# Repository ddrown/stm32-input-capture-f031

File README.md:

This was originally designed to accept a very low frequency pwm output (1-50Hz) and measure the SBC's frequency vs the TCXO's. That frequency data can then be fed into chrony's temperature compensation system to result in more stable time for NTP service.

Hardware is a custom designed SBC hat with microcontroller and TCXO

The TCXO's frequency vs temperature curve is measured and stored in flash in order to increase long term frequency accuracy.

The hat also contains an RTC with sub-second precision. Usually i2c RTCs will only tell you time to the nearest second, so you have to poll them to find out when the second changes. The RTC runs off the 32khz crystal, but can be measured in hardware against the TCXO with `clients/rtc compare`

Timers used
* TIM2 - main 32 bit timer, all 4 channels are setup as pwm output (10ms high, 990ms low)
* TIM14 - 16 bit timer, measures RTC vs TCXO on channel 1

Hat pins connected to SBC/stm32 micro:
* pin3 - I2C SDA
* pin5 - I2C SCL
* pin11 - stm32 rst (via jumper)
* pin12 - PPS output CH1
* pin13 - stm32 BOOT0 (via jumper)
* pin18 - SWD dio (via jumper)
* pin22 - SWD clk (via jumper)
* pin33 - PPS output CH2

settings in raspi-config:

i2c enabled
(optional for gps) serial login shell disabled, serial interface enabled

/boot/config.txt:
dtparam=i2c\_arm=on
dtparam=i2c\_arm\_baudrate=400000
\# optional for gps
dtoverlay=pps-gpio,gpiopin=13

stm32 source code:

* Src/system_stm32f0xx.c - bootup, start clocks
* Src/main.c - init peripherals, main loop
* Src/stm32f0xx_hal_msp.c - init irq, init gpio routing, init clocks, etc
* Src/stm32f0xx_it.c - irq handlers (mostly call into HAL)
* Src/adc.c - measure temperature, vcc, and rtc battery
* Src/flash.c - store TCXO parameters in flash
* Src/i2c_slave.c - i2c interface to talk to SBC
* Src/timer.c - manages TIM2, TIM14, and RTC
* Src/uart.c - debug uart interface
* Drivers/STM32F0xx_HAL_Driver - stm32 Hardware Abstraction Layer (HAL)

SBC tool code:

* clients/timestamps-i2c.c - compare SBC system time vs TCXO, request via i2c
* clients/input-capture-i2c.c - compare SBC system frequency vs TCXO, via SBC output pwm
* clients/pi-pwm-setup.c - wiringPi setup SBC output pwm
* clients/pi-pwm-disable.c - wiringPi disable SBC output pwm
* clients/odroid-c2-setup - sysfs setup SBC output pwm
* clients/rtc.c - read/set/sync/manage rtc
* clients/set-calibration-data.c - get/set TCXO calibration data in flash
* clients/ds3231.c - DS3231 RTC i2c client
* clients/pcf2129.c - PCF2129 RTC i2c client
* clients/calibration.c - measure RTC vs TCXO
* clients/dump-adc.c - test comparing floating vs fixed point math

SBC library code:

* clients/adc_calc.c - read ADC data over i2c
* clients/aging.c - estimate TCXO frequency from aging effects
* clients/avg.c - calculate averages
* clients/float.c - convert between native float and i2c compatible
* clients/i2c.c - i2c interface functions
* clients/i2c_registers.c - read stm32's exported data via i2c
* clients/rtc_data.c - convert between RTC data and system time
* clients/tempcomp.c - calculate TCXO's temperature compensation
* clients/timespec.c - struct timespec utilities
* clients/vref_calc.c - adc voltage calculations

Programming the stm32 can be done via openocd on the connected SBC.

Example openocd configuration:
* openocd.cfg - raspberry pi & stlink example
* openocd-odroid.cfg - gpio sysfs on odroid-c2 SBC
* openocd-stm32mp1.cfg - gpio sysfs on stm32mp157a-dk1 SBC

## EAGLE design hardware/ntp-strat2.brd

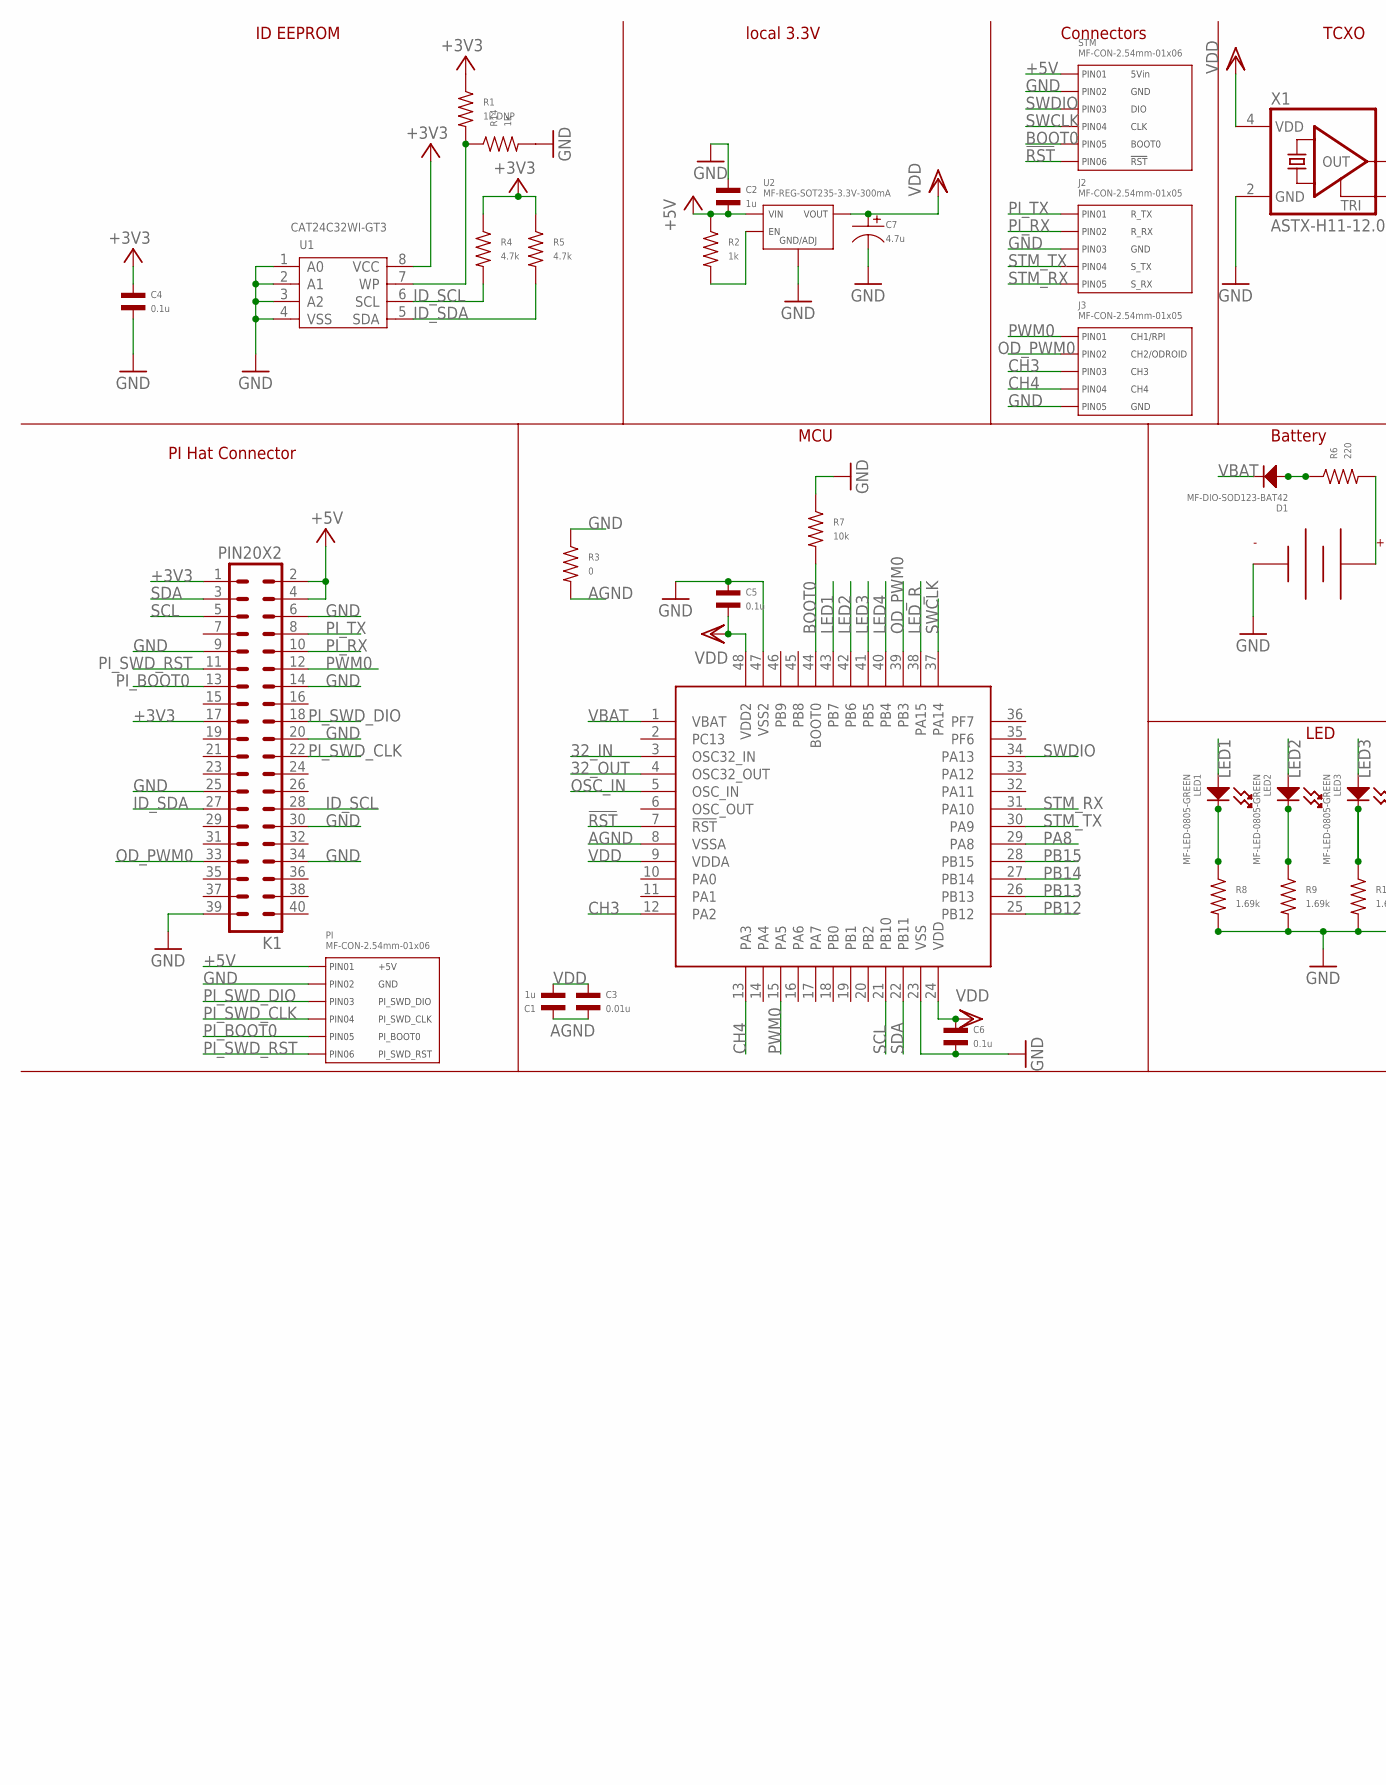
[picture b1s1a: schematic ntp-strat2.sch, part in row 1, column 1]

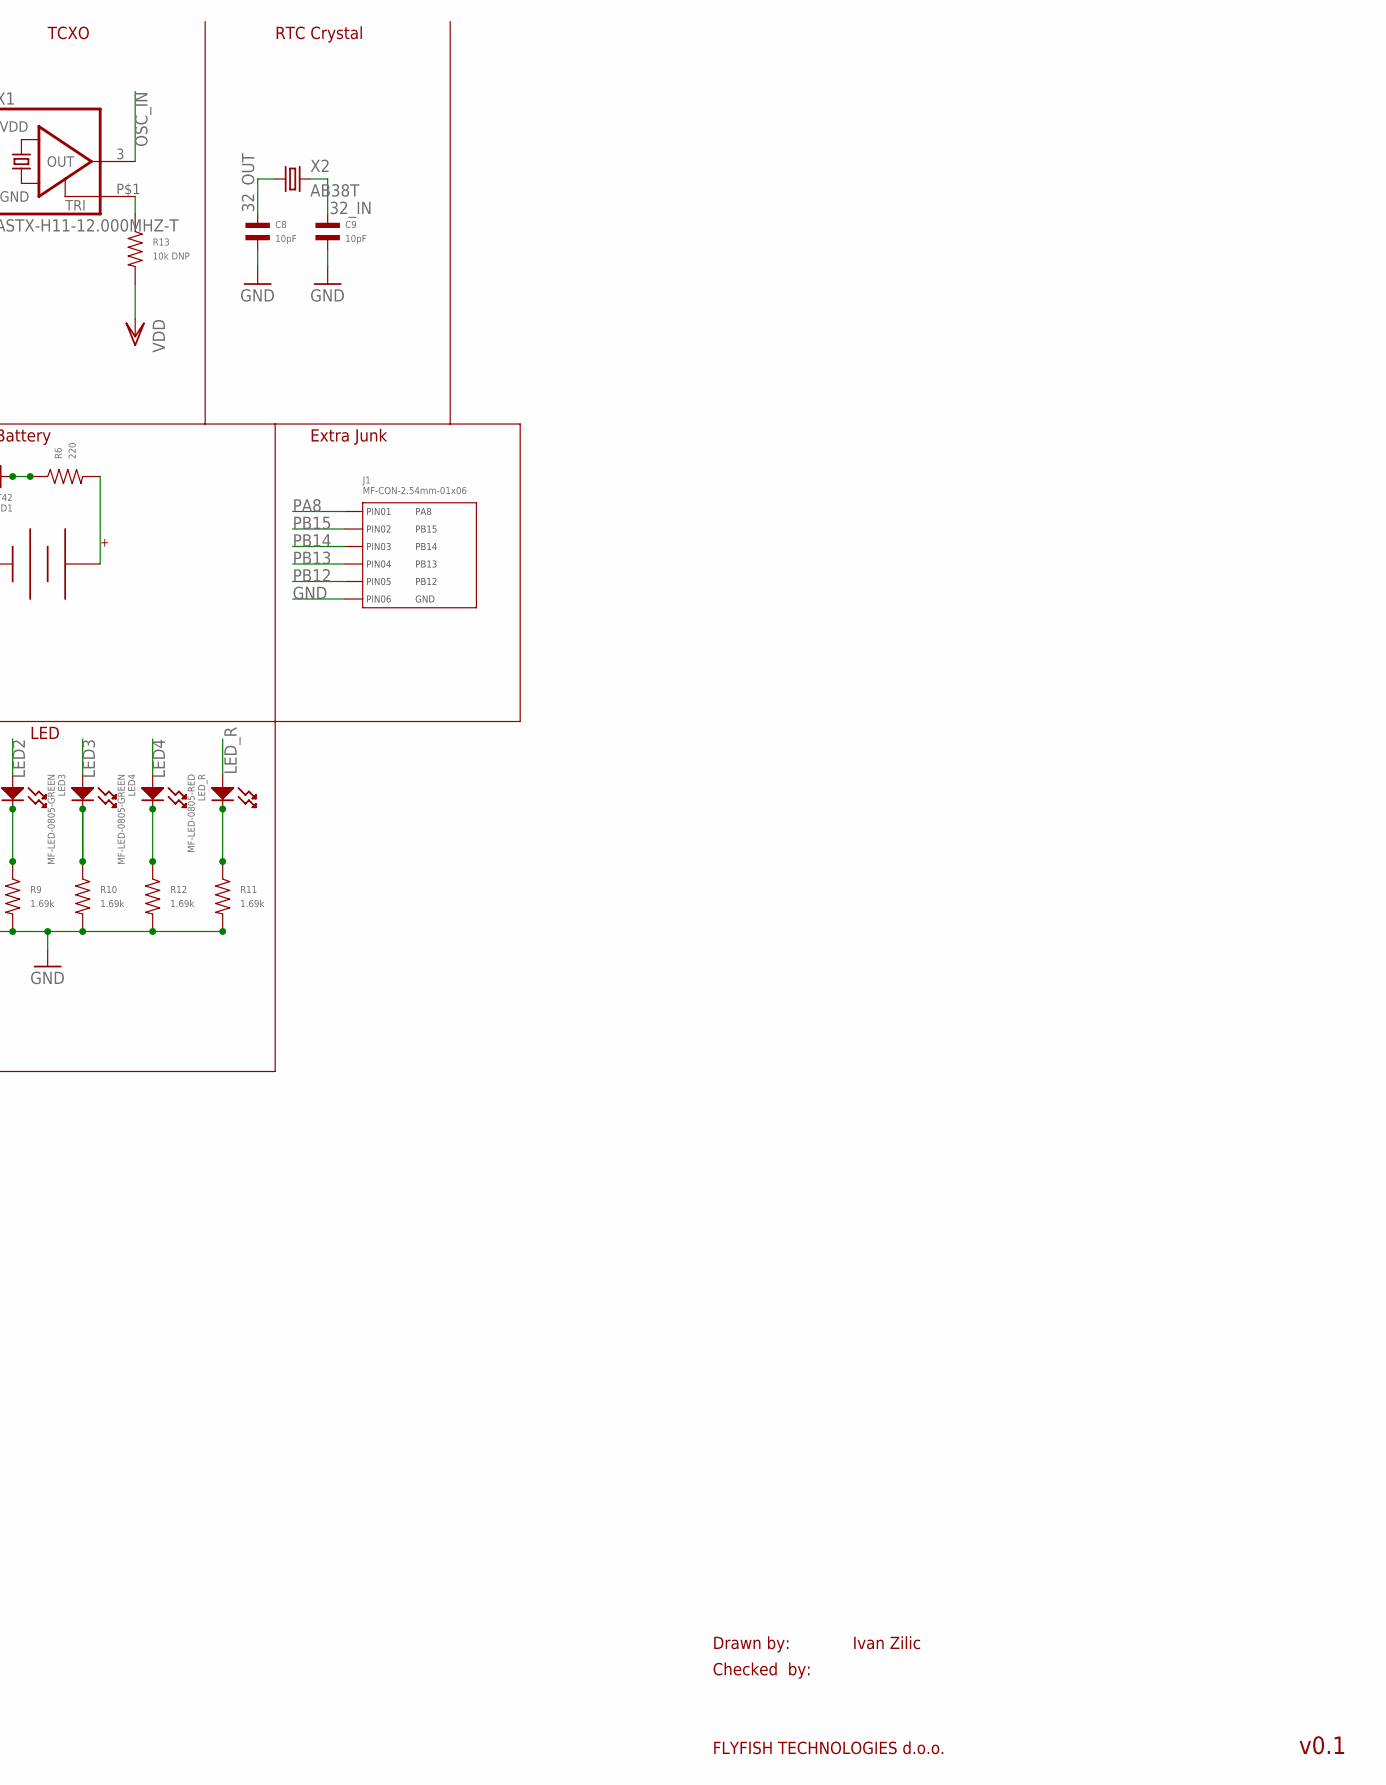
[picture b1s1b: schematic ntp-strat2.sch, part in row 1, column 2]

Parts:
C1, C2: 1u; C0603
C3: 0.01u; C0603
C4, C5, C6: 0.1u; C0603
C7: 4.7u; CP4MM
C8, C9: 10pF; C0603
D1: MF-DIO-SOD123-BAT42; SOD-123
J1: MF-CON-2.54mm-01x06; PTH_2.54MM_01X06
J2, J3: MF-CON-2.54mm-01x05; PTH_2.54MM_01X05
K1: PIN20X2; PIN_20X2
LED1, LED2, LED3, LED4: MF-LED-0805-GREEN; LED0805
LED_R: MF-LED-0805-RED; LED0805
PI: MF-CON-2.54mm-01x06; PTH_2.54MM_01X06
R1: 1k DNP; R0603
R2, R14: 1k; R0603
R3: 0; R0603
R4, R5: 4.7k; R0603
R6: 220; R0603
R7: 10k; R0603
R8, R9, R10, R11, R12: 1.69k; R0603
R13: 10k DNP; R0603
STM: MF-CON-2.54mm-01x06; PTH_2.54MM_01X06
U1: CAT24C32WI-GT3; SOIC8-1.27-5X4MM
U2: MF-REG-SOT235-3.3V-300mA; SOT-23-5
U3: STM32F031C6T6; LQFP48-7X7
U4: BU2032SM-BT-GTR; BU2032SM
X1: ASTX-H11-12.000MHZ-T; ASVTX
X2: AB38T

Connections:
32_IN: C9.P$1, U3.3 (OSC32_IN), X2.P2 (2)
32_OUT: C8.P$1, U3.4 (OSC32_OUT), X2.P1 (1)
!RST: STM.P$6 (PIN6), U3.7 (!RST)
+3V3: C4.P$1, K1.1, K1.17, R1.P$1, R4.P$1, R5.P$1, U1.8 (VCC)
+5V: C2.P$2, K1.2, K1.4, PI.P$1 (PIN1), R2.P$1, STM.P$1 (PIN1), U2.P$1 (VIN)
AGND: C1.P$1, C3.P$2, R3.P$2, U3.8 (VSSA)
BOOT0: R7.P$2, STM.P$5 (PIN5), U3.44 (BOOT0)
CH3: J3.P$3 (PIN3), U3.12 (PA2)
CH4: J3.P$4 (PIN4), U3.13 (PA3)
GND: C2.P$1, C4.P$2, C5.P$1, C6.P$2, C7.P$2, C8.P$2, C9.P$2, J1.P$6 (PIN6), J2.P$3 (PIN3), J3.P$5 (PIN5), K1.6, K1.9, K1.14, K1.20, K1.25, K1.30, K1.34, K1.39, PI.P$2 (PIN2), R3.P$1, R7.P$1, R8.P$2, R9.P$2, R10.P$2, R11.P$2, R12.P$2, R14.P$2, STM.P$2 (PIN2), U1.1 (A0), U1.2 (A1), U1.3 (A2), U1.4 (VSS), U2.P$2 (GND/ADJ), U3.23 (VSS), U3.47 (VSS2), U4.MINUS, X1.2 (GND)
ID_SCL: K1.28, R4.P$2, U1.6 (SCL)
ID_SDA: K1.27, R5.P$2, U1.5 (SDA)
LED1: LED1.ANODE, U3.43 (PB7)
LED2: LED2.ANODE, U3.42 (PB6)
LED3: LED3.ANODE, U3.41 (PB5)
LED4: LED4.ANODE, U3.40 (PB4)
LED_R: LED_R.ANODE, U3.38 (PA15)
unnamed: R2.P$2, U2.P$3 (EN)
unnamed: LED1.CATHODE, R8.P$1
unnamed: R1.P$2, R14.P$1, U1.7 (WP)
unnamed: D1.ANODE, R6.P$1
unnamed: LED2.CATHODE, R9.P$1
unnamed: LED3.CATHODE, R10.P$1
unnamed: LED_R.CATHODE, R11.P$1
unnamed: LED4.CATHODE, R12.P$1
unnamed: R6.P$2, U4.PLUS
unnamed: R13.P$1, X1.P$1 (TRI)
OD_PWM0: J3.P$2 (PIN2), K1.33, U3.39 (PB3)
OSC_IN: U3.5 (OSC_IN), X1.3 (OUT)
PA8: J1.P$1 (PIN1), U3.29 (PA8)
PB12: J1.P$5 (PIN5), U3.25 (PB12)
PB13: J1.P$4 (PIN4), U3.26 (PB13)
PB14: J1.P$3 (PIN3), U3.27 (PB14)
PB15: J1.P$2 (PIN2), U3.28 (PB15)
PI_BOOT0: K1.13, PI.P$5 (PIN5)
PI_RX: J2.P$2 (PIN2), K1.10
PI_SWD_CLK: K1.22, PI.P$4 (PIN4)
PI_SWD_DIO: K1.18, PI.P$3 (PIN3)
PI_SWD_RST: K1.11, PI.P$6 (PIN6)
PI_TX: J2.P$1 (PIN1), K1.8
PWM0: J3.P$1 (PIN1), K1.12, U3.15 (PA5)
SCL: K1.5, U3.21 (PB10)
SDA: K1.3, U3.22 (PB11)
STM_RX: J2.P$5 (PIN5), U3.31 (PA10)
STM_TX: J2.P$4 (PIN4), U3.30 (PA9)
SWCLK: STM.P$4 (PIN4), U3.37 (PA14)
SWDIO: STM.P$3 (PIN3), U3.34 (PA13)
VBAT: D1.CATHODE, U3.1 (VBAT)
VDD: C1.P$2, C3.P$1, C5.P$2, C6.P$1, C7.P$1, R13.P$2, U2.P$5 (VOUT), U3.9 (VDDA), U3.24 (VDD), U3.48 (VDD2), X1.4 (VDD)

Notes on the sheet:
Drawn by:
Checked by:
FLYFISH TECHNOLOGIES d.o.o.
Ivan Zilic
v0.1
ID EEPROM
PI Hat Connector
local 3.3V
Connectors
TCXO
RTC Crystal
Battery
MCU
LED
Extra Junk

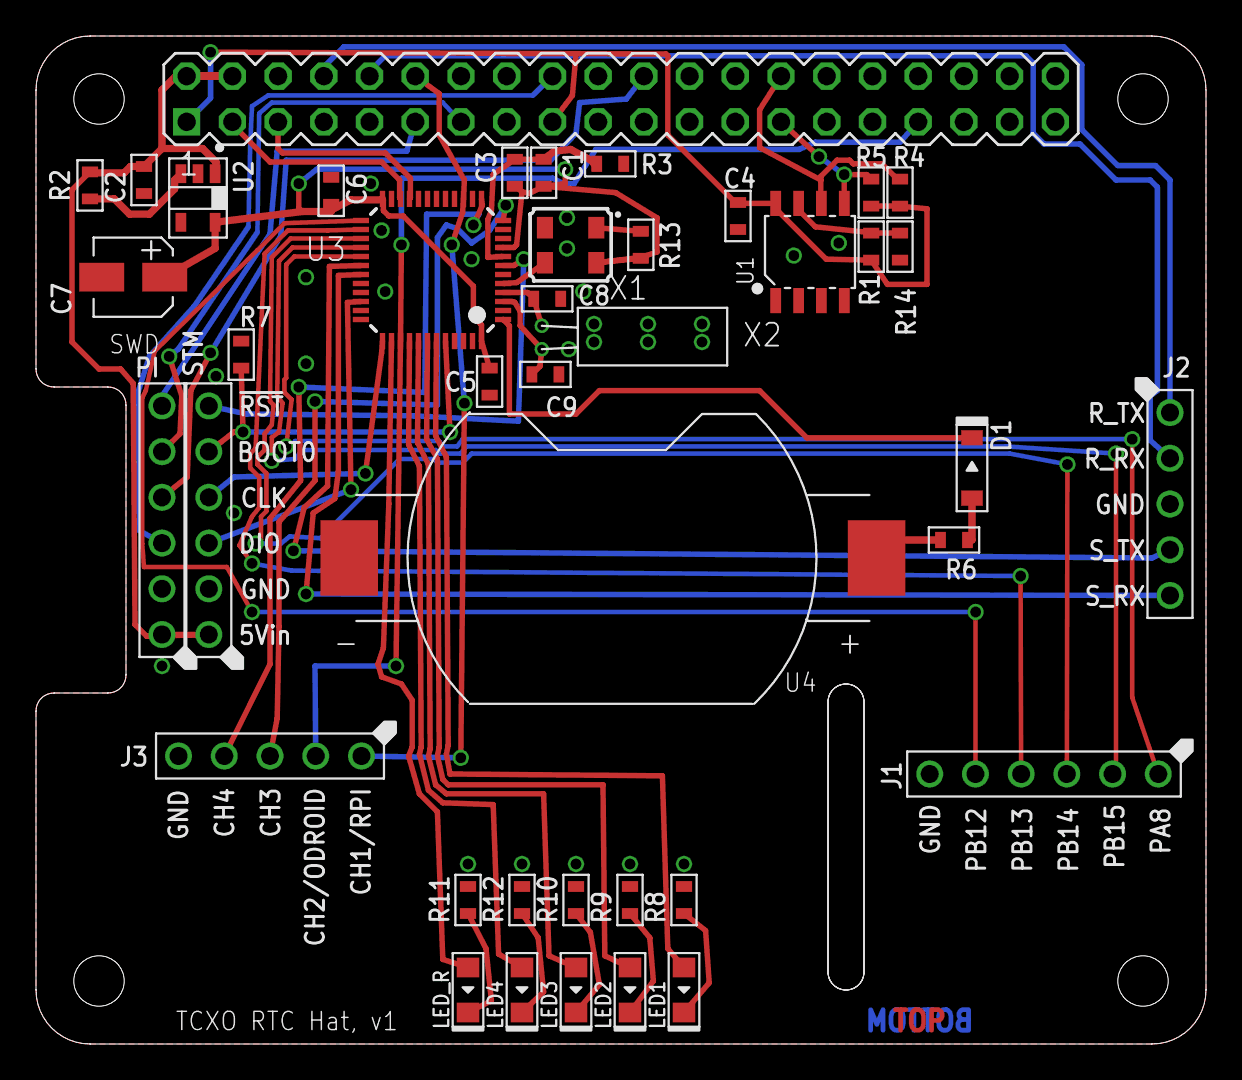
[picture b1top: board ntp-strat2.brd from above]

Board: 2 copper layers, 65.0 x 56.0 mm, 41 parts (0 on the bottom side), 49 nets.

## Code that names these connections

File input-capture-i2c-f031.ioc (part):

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Mcu.Name=STM32F031C(4-6)Tx
Mcu.Package=LQFP48
Mcu.UserName=STM32F031C6Tx
PA10.Mode=Asynchronous
PA10.Signal=USART1_RX
PA13.Mode=Serial_Wire
PA13.Signal=SYS_SWDIO
PA14.Mode=Serial_Wire
PA14.Signal=SYS_SWCLK
PA15.GPIOParameters=GPIO_Label
PA15.GPIO_Label=LED_R
PA15.Signal=GPIO_Output
PA2.Signal=S_TIM2_CH3
PA3.Signal=S_TIM2_CH4
PA5.Signal=S_TIM2_CH1_ETR
PA9.Mode=Asynchronous
PA9.Signal=USART1_TX
PB10.GPIOParameters=GPIO_Pu
PB10.GPIO_Pu=GPIO_PULLUP
PB10.Mode=I2C
PB10.Signal=I2C1_SCL
PB11.GPIOParameters=GPIO_Pu
PB11.GPIO_Pu=GPIO_PULLUP
PB11.Mode=I2C
PB11.Signal=I2C1_SDA
PB3.Signal=S_TIM2_CH2
PB4.GPIOParameters=GPIO_Label
PB4.GPIO_Label=LED4
PB4.Signal=GPIO_Output
PB5.GPIOParameters=GPIO_Label
PB5.GPIO_Label=LED3
PB5.Signal=GPIO_Output
PB6.GPIOParameters=GPIO_Label
PB6.GPIO_Label=LED2
PB6.Signal=GPIO_Output
PB7.GPIOParameters=GPIO_Label
PB7.GPIO_Label=LED1
PB7.Signal=GPIO_Output
PC14-OSC32_IN.Mode=LSE-External-Oscillator
PC14-OSC32_IN.Signal=RCC_OSC32_IN
PC15-OSC32_OUT.Mode=LSE-External-Oscillator
PC15-OSC32_OUT.Signal=RCC_OSC32_OUT
PF0-OSC_IN.Mode=HSE-External-Clock-Source
PF0-OSC_IN.Signal=RCC_OSC_IN
RCC.HSE_VALUE=12000000
RCC.SYSCLKFreq_VALUE=48000000
RCC.SYSCLKSource=RCC_SYSCLKSOURCE_PLLCLK
board=input-capture-i2c-f031

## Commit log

2017-03-18 f031 version
2017-03-19 import f030 files
2017-03-19 add LED GPIOs
2017-04-29 ADC and RTC support
2017-04-29 cubemx version update and pin redefinitions
2017-04-29 need 33 bits for full 100 year range
2017-04-29 fix warnings
2017-04-30 client upgrade
2017-04-30 calibration scripts
2017-05-01 missing header
2017-05-01 update for primary channel settings
2017-05-01 wrong sign
2017-05-01 add best fit equations
2017-05-01 stlink version
2017-05-01 move rtc year before set_rtc, allow rtc values to be set via i2c, copy i2c page with interrupts off on set page operation
2017-05-01 RTC_SHIFTADD1S_SET is not bit 15
2017-05-01 cleanup makefile
2017-05-01 set rtc time, set rtc calibration, set rtc subsecond adjust
2017-05-01 move graphs into subdirectories
2017-05-02 incorrect units
2017-05-02 plot scripts
2017-05-04 new rtc command: sync (just phase)
2017-05-04 use median instead of average
2017-05-05 5 polls, 10.541ms apart
2017-05-05 higher precision steps
2017-05-06 new rtc command: setsystem, systemd boot/shutdown script, documentation cleanup
2017-05-09 GMT timezone is no longer needed
2017-05-09 rtc sync script
2017-05-09 input-capture-i2c for the f031
2017-05-09 update comments
2017-05-27 added verbose mode, default is print every 64s
2017-05-27 systemd service
2017-06-13 compare LSE to TCXO and set RTC calibration values
2017-06-13 flush output for logging
2017-06-13 startup scripts
2017-06-22 limit adjustment range to be +32767 .. -32768
2017-07-03 start of docs
2017-09-10 add aging to rtc
2017-09-16 simple client for frequency logging
2017-09-16 use an aging linear estimation
2017-09-23 add aging to input-capture-i2c
2017-09-23 add aging to input-capture-i2c #2
2017-10-10 Firmware upgrade V1.7.0 -> V1.9.0
2017-10-11 page4/page 5 registers
    page4: new item: tim2 count on top of second
    page5: new items:
    current tim2 count
    current millis count
    5x 32 bit RTC general purpose registers
2017-10-11 new rtc command: offset (offset between RTC and system time)
2017-10-16 hse offset, nanosecond timers
2018-01-25 documentation is wrong
2018-01-25 raw frequency information
2018-01-25 testing fixed point math
2022-04-27 make i2c bus configurable
2022-04-27 move tempcomp to its own files
2022-04-27 odroid openocd config
2022-04-27 example data
2022-04-27 query via i2c, print offset & adjust for tempcomp
2022-04-27 remove pi-pwm-setup from default build, add dump-adc+timestamps-i2c
2022-04-27 update documentation
2022-04-28 hardware design files
2022-04-28 upgrade STM32Cube Firmware to V1.11.3
2022-04-28 Error_Handler changed with newer firmware
2022-04-29 don't write rwflash section to flash
2022-04-29 use /usr/local/sbin/rtc
2022-04-29 remove hardcoded aging parameter
2022-04-29 flash and reboot from odroid
2022-05-05 flash and reboot from stm32mp157
2022-05-06 switching to output pps with internal tempcomp
2022-05-06 vscode config & simple tests
2022-05-06 switch from input compare to output pwm
2022-05-07 clients for pps output
2022-05-07 pps output firmware
2022-05-07 show calculated values, correct sign of c
2022-05-07 portable int64 printf format
2022-05-09 choose which channel to use via compile flag
2022-05-09 document pinout
2022-05-15 add pps-gpio on pin12 overlay for odroid c2
2022-05-16 set offset and poll timer state
2022-05-27 change poll output for logging temp data
2022-06-18 set aging freq adjust every minute
2022-06-18 updating rtc adjust/offset for micro tempcomp
2022-07-06 switch write_i2c to take a const pointer
2022-07-06 sync rtc to tcxo
2022-07-07 addclk has the wrong value
2022-07-07 linear() should return in ppm
